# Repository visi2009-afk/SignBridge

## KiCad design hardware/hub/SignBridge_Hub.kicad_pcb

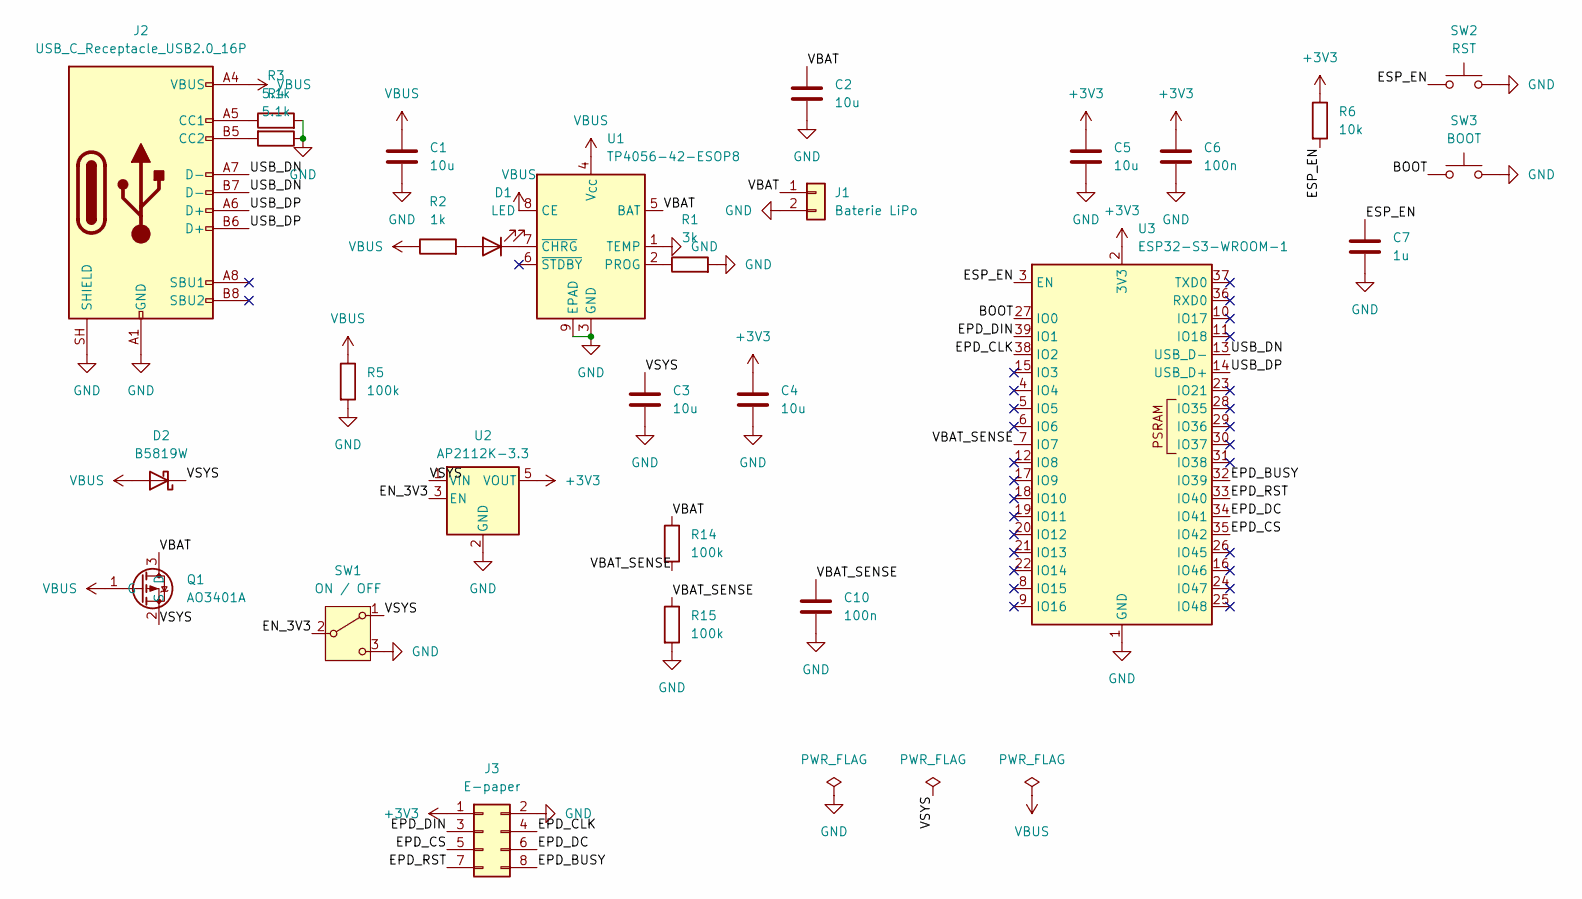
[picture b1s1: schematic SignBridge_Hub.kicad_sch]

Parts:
C1, C2, C3, C4, C5: 10u; C_0603_1608Metric_Pad1.08x0.95mm_HandSolder
C6, C10: 100n; C_0603_1608Metric_Pad1.08x0.95mm_HandSolder
C7: 1u; C_0603_1608Metric_Pad1.08x0.95mm_HandSolder
D1: LED; LED_0603_1608Metric_Pad1.05x0.95mm_HandSolder
D2: B5819W; D_SOD-123
J1: Baterie LiPo; JST_PH_S2B-PH-SM4-TB_1x02-1MP_P2.00mm_Horizontal
J2: USB_C_Receptacle_USB2.0_16P; USB_C_Receptacle_HRO_TYPE-C-31-M-12
J3: E-paper; PinHeader_2x04_P2.54mm_Vertical
Q1: AO3401A; SOT-23
R1: 3k; R_0603_1608Metric_Pad0.98x0.95mm_HandSolder
R2: 1k; R_0603_1608Metric_Pad0.98x0.95mm_HandSolder
R3, R4: 5.1k; R_0603_1608Metric_Pad0.98x0.95mm_HandSolder
R5, R14, R15: 100k; R_0603_1608Metric_Pad0.98x0.95mm_HandSolder
R6: 10k; R_0603_1608Metric_Pad0.98x0.95mm_HandSolder
SW1: ON / OFF; SW_SPDT_PCM12
SW2: RST; SW_Push_1P1T_XKB_TS-1187A
SW3: BOOT; SW_Push_1P1T_XKB_TS-1187A
U1: TP4056-42-ESOP8; SOIC-8-1EP_3.9x4.9mm_P1.27mm_EP2.41x3.3mm
U2: AP2112K-3.3; SOT-23-5
U3: ESP32-S3-WROOM-1

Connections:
+3V3: C4.1, C5.1, C6.1, J3.1, R6.1, U2.5 (VOUT), U3.2 (3V3)
/BOOT: SW3.1, U3.27 (IO0)
/EN_3V3: SW1.2 (B), U2.3 (EN)
/EPD_BUSY: J3.8, U3.32 (IO39)
/EPD_CLK: J3.4, U3.38 (IO2)
/EPD_CS: J3.5, U3.35 (IO42)
/EPD_DC: J3.6, U3.34 (IO41)
/EPD_DIN: J3.3, U3.39 (IO1)
/EPD_RST: J3.7, U3.33 (IO40)
/ESP_EN: C7.1, R6.2, SW2.1, U3.3 (EN)
/USB_DN: J2.A7 (D-), J2.B7 (D-), U3.13 (USB_D-)
/USB_DP: J2.A6 (D+), J2.B6 (D+), U3.14 (USB_D+)
/VBAT: C2.1, J1.1, Q1.3 (D), R14.1, U1.5 (BAT)
/VBAT_SENSE: C10.1, R14.2, R15.1, U3.7 (IO7)
/VSYS: C3.1, D2.1 (K), Q1.2 (S), SW1.1 (A), U2.1 (VIN)
GND: C1.2, C2.2, C3.2, C4.2, C5.2, C6.2, C7.2, C10.2, J1.2, J2.A1 (GND), J2.A12 (GND), J2.B1 (GND), J2.B12 (GND), J2.SH (SHIELD), J3.2, R1.2, R3.2, R4.1, R5.2, R15.2, SW1.3 (C), SW2.2, SW3.2, U1.1 (TEMP), U1.3 (GND), U1.9 (EPAD), U2.2 (GND), U3.1 (GND), U3.40 (GND), U3.41 (GND)
unnamed: D1.2 (A), R2.2
unnamed: D1.1 (K), U1.7 (~CHRG)
unnamed: J2.A5 (CC1), R3.1
unnamed: J2.B5 (CC2), R4.2
unnamed: R1.1, U1.2 (PROG)
VBUS: C1.1, D2.2 (A), J2.A4 (VBUS), J2.A9 (VBUS), J2.B4 (VBUS), J2.B9 (VBUS), Q1.1 (G), R2.1, R5.1, U1.4 (V_{CC}), U1.8 (CE)

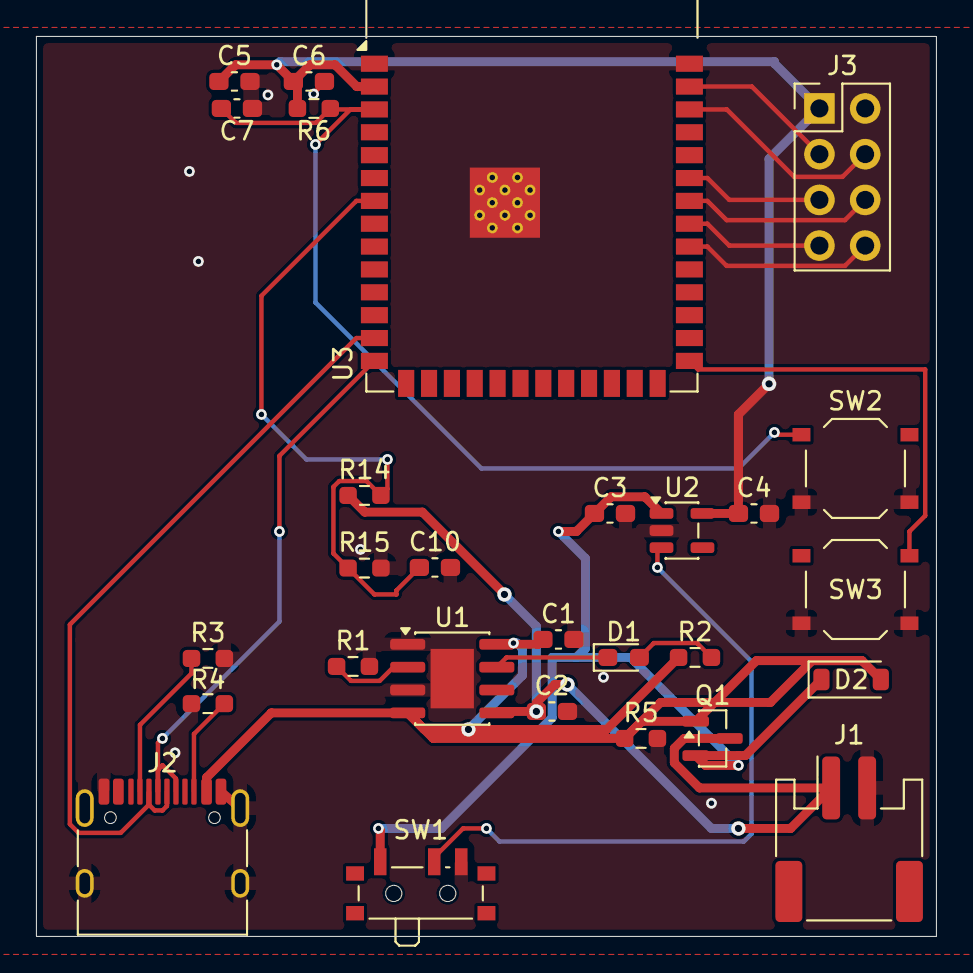
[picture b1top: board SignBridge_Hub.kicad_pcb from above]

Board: 2 copper layers, 50.0 x 50.0 mm, 28 parts (0 on the bottom side), 22 nets.

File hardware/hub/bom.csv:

Reference,Qty,Value,Footprint,LCSC,Link
"C1,C2,C3,C4,C5",5,10u,Capacitor_SMD:C_0603_1608Metric_Pad1.08x0.95mm_HandSolder,C19702,https://www.lcsc.com/product-detail/C19702.html
"C6,C10",2,100n,Capacitor_SMD:C_0603_1608Metric_Pad1.08x0.95mm_HandSolder,C14663,https://www.lcsc.com/product-detail/C14663.html
C7,1,1u,Capacitor_SMD:C_0603_1608Metric_Pad1.08x0.95mm_HandSolder,C15849,https://www.lcsc.com/product-detail/C15849.html
D1,1,LED,LED_SMD:LED_0603_1608Metric_Pad1.05x0.95mm_HandSolder,C2286,https://www.lcsc.com/product-detail/C2286.html
D2,1,B5819W,Diode_SMD:D_SOD-123,C8598,https://www.lcsc.com/product-detail/C8598.html
J1,1,Baterie LiPo,Connector_JST:JST_PH_S2B-PH-SM4-TB_1x02-1MP_P2.00mm_Horizontal,C295747,https://www.lcsc.com/product-detail/C295747.html
J2,1,USB_C_Receptacle_USB2.0_16P,Connector_USB:USB_C_Receptacle_HRO_TYPE-C-31-M-12,C165948,https://www.lcsc.com/product-detail/C165948.html
J3,1,E-paper,Connector_PinHeader_2.54mm:PinHeader_2x04_P2.54mm_Vertical,C53207328,https://www.lcsc.com/product-detail/C53207328.html
Q1,1,AO3401A,Package_TO_SOT_SMD:SOT-23,C15127,https://www.lcsc.com/product-detail/C15127.html
R1,1,3k,Resistor_SMD:R_0603_1608Metric_Pad0.98x0.95mm_HandSolder,C4211,https://www.lcsc.com/product-detail/C4211.html
R2,1,1k,Resistor_SMD:R_0603_1608Metric_Pad0.98x0.95mm_HandSolder,C21190,https://www.lcsc.com/product-detail/C21190.html
"R3,R4",2,5.1k,Resistor_SMD:R_0603_1608Metric_Pad0.98x0.95mm_HandSolder,C23186,https://www.lcsc.com/product-detail/C23186.html
"R5,R14,R15",3,100k,Resistor_SMD:R_0603_1608Metric_Pad0.98x0.95mm_HandSolder,C25803,https://www.lcsc.com/product-detail/C25803.html
R6,1,10k,Resistor_SMD:R_0603_1608Metric_Pad0.98x0.95mm_HandSolder,C25804,https://www.lcsc.com/product-detail/C25804.html
SW1,1,ON / OFF,Button_Switch_SMD:SW_SPDT_PCM12,C221841,https://www.lcsc.com/product-detail/C221841.html
SW2,1,RST,Button_Switch_SMD:SW_Push_1P1T_XKB_TS-1187A,C318884,https://www.lcsc.com/product-detail/C318884.html
SW3,1,BOOT,Button_Switch_SMD:SW_Push_1P1T_XKB_TS-1187A,C318884,https://www.lcsc.com/product-detail/C318884.html
U1,1,TP4056-42-ESOP8,Package_SO:SOIC-8-1EP_3.9x4.9mm_P1.27mm_EP2.41x3.3mm,C16581,https://www.lcsc.com/product-detail/C16581.html
U2,1,AP2112K-3.3,Package_TO_SOT_SMD:SOT-23-5,C51118,https://www.lcsc.com/product-detail/C51118.html
U3,1,ESP32-S3-WROOM-1,RF_Module:ESP32-S3-WROOM-1,C2913202,https://www.lcsc.com/product-detail/C2913202.html

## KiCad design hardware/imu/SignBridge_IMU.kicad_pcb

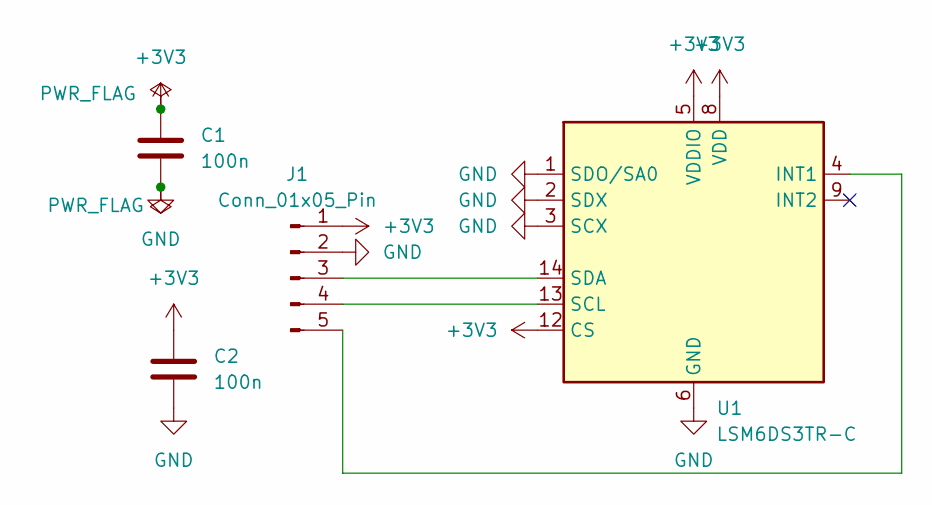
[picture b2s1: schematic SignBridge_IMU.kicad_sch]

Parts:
C1, C2: 100n; C_0603_1608Metric_Pad1.08x0.95mm_HandSolder
J1: Conn_01x05_Pin; PinHeader_1x05_P2.54mm_Vertical
U1: LSM6DS3TR-C; LGA-14_3x2.5mm_P0.5mm_LayoutBorder3x4y

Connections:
+3V3: C1.1, C2.1, J1.1, U1.5 (VDDIO), U1.8 (VDD), U1.12 (CS)
GND: C1.2, C2.2, J1.2, U1.1 (SDO/SA0), U1.2 (SDX), U1.3 (SCX), U1.6 (GND), U1.7 (GND)
unnamed: J1.3, U1.14 (SDA)
unnamed: J1.4, U1.13 (SCL)
unnamed: J1.5, U1.4 (INT1)

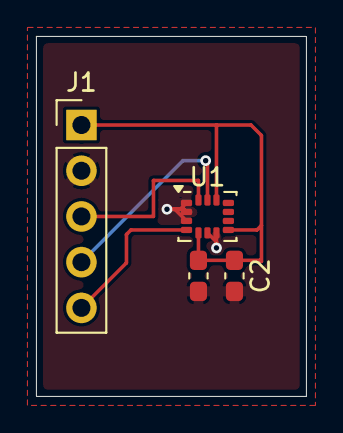
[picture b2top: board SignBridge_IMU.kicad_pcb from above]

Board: 2 copper layers, 15.0 x 20.0 mm, 4 parts (0 on the bottom side), 5 nets.

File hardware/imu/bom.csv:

Reference,Qty,Value,Footprint,LCSC,Link
"C1,C2",2,100n,Capacitor_SMD:C_0603_1608Metric_Pad1.08x0.95mm_HandSolder,C14663,https://www.lcsc.com/product-detail/C14663.html
J1,1,Conn_01x05_Pin,Connector_PinHeader_2.54mm:PinHeader_1x05_P2.54mm_Vertical,C50981,https://www.lcsc.com/product-detail/C50981.html
U1,1,LSM6DS3TR-C,Package_LGA:LGA-14_3x2.5mm_P0.5mm_LayoutBorder3x4y,C967633,https://www.lcsc.com/product-detail/C967633.html
